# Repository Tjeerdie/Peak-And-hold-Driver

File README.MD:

# Project PWM peak and hold injector driver
The peak and hold project started because I could not find an open-source PWM peak and hold injector driver for low-Z injectors. For low-z injectors normally resistors in series with the injectors are used. But resistors create a lot of heat and are not very adjustable. 

I still do encourage everyone to use resistors if possible because the results are good and resistors have less components that can fail<br/>
<br/>
This design is specific to work with LPG injectors but could be used for any other low-Z injectors like TBI type and other high flow injectors. It could even be used for any coil type actuator like relays or valves <br/>

The board is designed in Kicad. So to see the schematic or to adjust the design to your liking open the Kicad project.<br/>

Latest release is V0.3.1<br/>
__IMPORANT NOTE: Board V0.3.1 is not tested yet!! A modified V0.3 is used for bench testing the V0.3.1 schematic. I did not test the board on a car yet__<br/>
__specifications:__
- Max peak current ~5A<br/>
- Max continuous hold current ~1A (No extra cooling)<br/>
- Max continuous hold current ~2A (With extra cooling)<br/>
- Hold PWM duty cycle 5%-95%<br/>
- PWM frequency 7khz<br/>
- 4 Individual injector channels<br/>
- Peak and hold current are adjustable

## Getting Started
This section explains all we need to do to setup a fabricated PCB

### Get all the parts
1. Order the PCB. For example use https://www.pcbway.com/ or https://jlcpcb.com/ Upload the PeakHoldPWMDriver_V0.x.y.zip located in the gebers folder and order the design.<br/>
2. Get all the parts from you favorite supplier. A BOM list is included in the geber folder<br/>
3. Assemble the PCB, hand soldering is possible.<br/>

### Connect the board
The board is intended to be connected to any ECU that uses a switch to ground for each injector channel. This is the case for most types of ECU. Further down this readme there is a description how to use microcontroller pins to drive the injectors directly. <br/>

__Connector J1__
1. injector channel 1 IN<br/>
2. injector channel 2 IN<br/>
3. injector channel 3 IN<br/>
4. injector channel 4 IN<br/>
5. Power - <br/>
6. Power + (14.8V switched with ignition switch)<br/>

__Connector J2__
1. inj channel 1 +<br/>
2. inj channel 1 -<br/>
3. inj channel 2 +<br/>
4. inj channel 2 -<br/>
5. inj channel 3 +<br/>
6. inj channel 3 -<br/>
7. inj channel 4 +<br/>
8. inj channel 4 -<br/>

Power on the board. Led must be lit when powered.<br/>

### Set the PEAK current
1. Measure __TP1__ and use __RV2__ to set to value needed. 100mV = 1A<br/>
2. Make sure this PEAK current is not too close to the maximum current. If that is the case you run the risk the peak current is never reached and the HOLD current is never set. Maximum advised peak current = 10.0[V] / R-inj[Ohm]<br/>

### Set the HOLD current
1. Measure the resistance of the injector(s) per channel (R-inj)[Ohm]. <br/>
2. Find the hold current needed for the injector in the datasheet. Usually about 50% to 25% of the peak current would be enough<br/>
3. Calculate the duty cycle needed using: ((R-inj + 0.20)* HoldCurrent)/2,4<br/>
4. Measure __TP2__ and use __RV1__ to set it to voltage calculated in step 3.<br/>
5. If it is possible in your setup or on a bench, connect __injector channel 1 IN__ to the __Power -__ use a multi-meter in series with your connected injector on channel 1 to measure the current. This must be close the the set current. If this is not correct adjust __RV1__ accordingly. Be careful when doing this test! When fuel pressure is present during testing the injector under test wil spray (a lot) of fuel! Its best to test with not pressurised injectors<br/>

### Direct microcontroller input
It is possible to use the board directly with an microcontroller. (non inverted inputs) The board inputs are designed for 5V. 3.3V can work but is on the edge so any voltage drop or temperature change may make it stop working correctly. <br/>

With a sharp object scratch the bridge between __pin 1__ and __pin 2__ of __JP1__, __JP2__, __JP3__, __JP4__ on the back of the board. Use a multi-meter to double check the connection is broken. Use a soldering iron and a bit of solder to connect __pin 3__ and __pin 2__ for __JP1__ to __JP4__. The second step is to remove R8, R25, R11, R28 from the board<br/> 
       
## Simulation	
An LTspice simulation of PWM peak and hold drivers is also in the LTspice folder. It is a good learning experience to see the wave forms and the current thru the coil. This also shows the maximum voltage level expected on the mosfets. This can be significant voltage levels depdending on the clamping voltage of the main driver. <br/>

## License
This project is licensed under the GNU GENERAL PUBLIC LICENSE - see the [LICENSE.md](LICENSE.md) file for details<br/>

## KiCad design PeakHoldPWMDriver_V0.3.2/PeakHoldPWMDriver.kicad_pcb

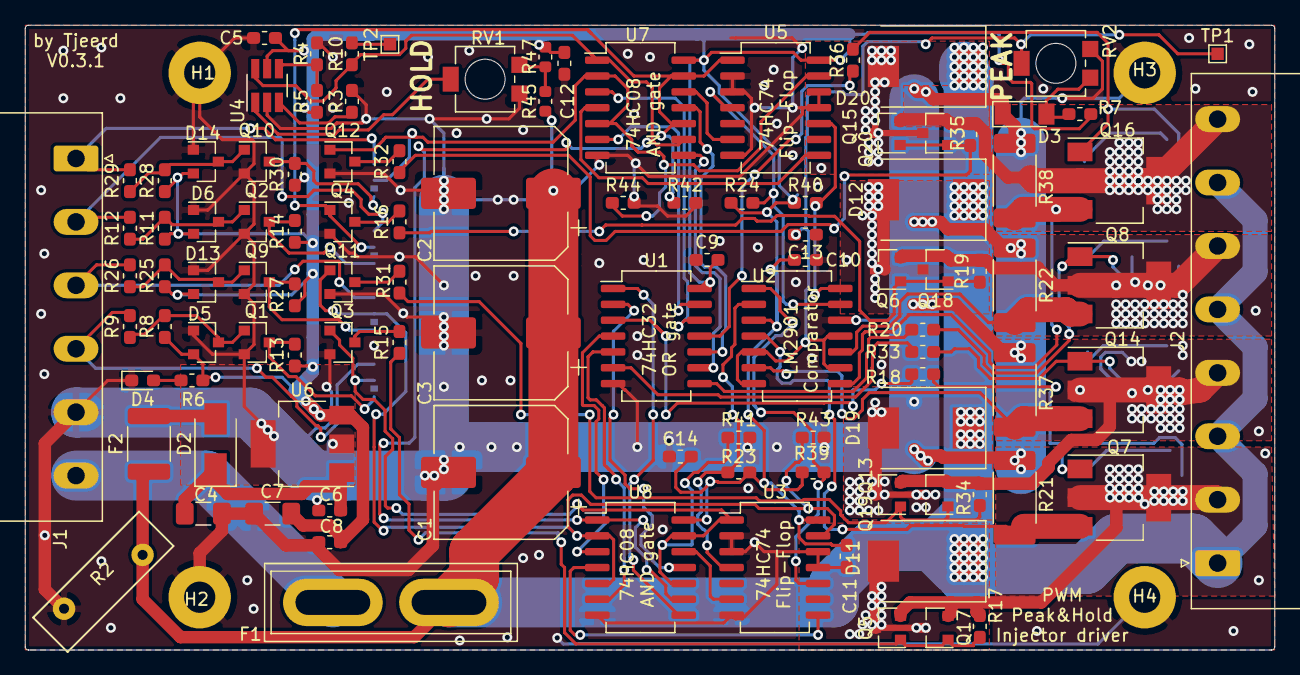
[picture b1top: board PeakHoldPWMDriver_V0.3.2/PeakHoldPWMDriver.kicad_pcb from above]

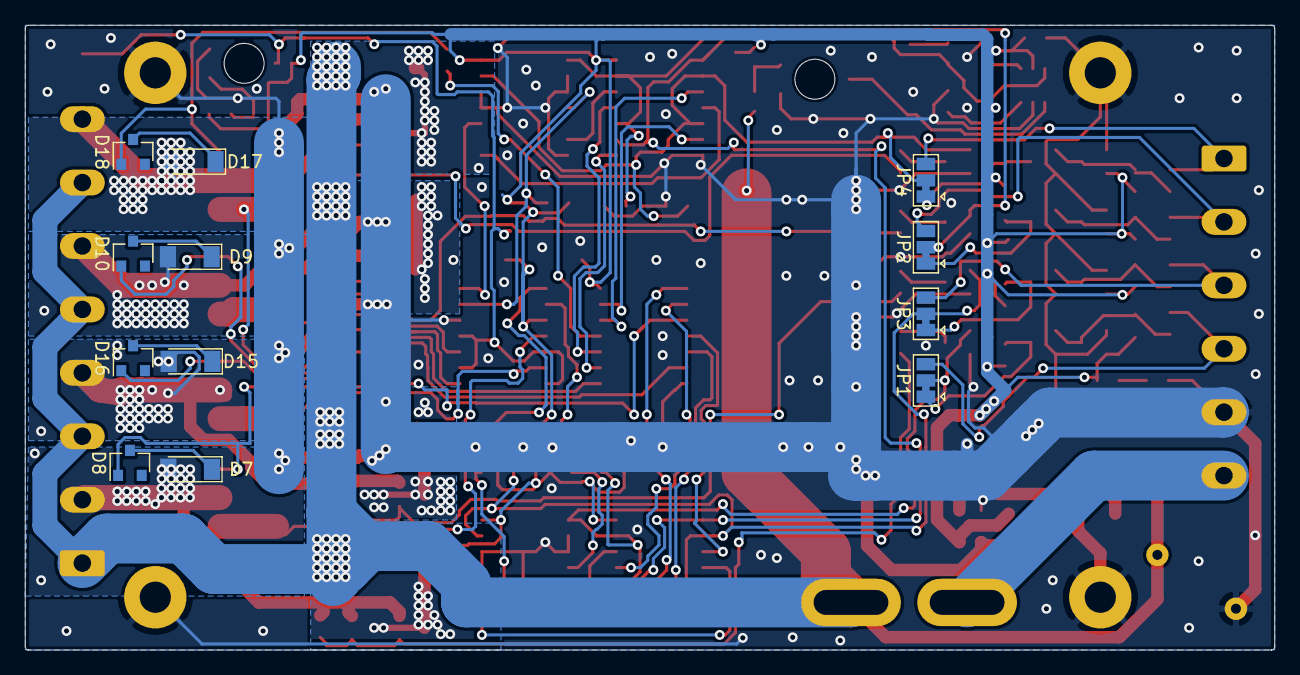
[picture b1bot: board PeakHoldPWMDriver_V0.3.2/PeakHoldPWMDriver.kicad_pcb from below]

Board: 2 copper layers, 100.1 x 50.0 mm, 122 parts (12 on the bottom side), 79 nets.

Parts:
C1, C2, C3: 1mF; CP_Elec_10x12.5
C4, C7: 10uf; C_1206_3216Metric_Pad1.42x1.75mm_HandSolder
C5, C6, C8, C9, C10, C11, C12, C13, C14: 220nf; C_0603_1608Metric_Pad1.05x0.95mm_HandSolder
D2: 1N4007; D_SMA
D3: LL4148; D_MiniMELF
D4: BLUE; LED_0603_1608Metric_Pad1.05x0.95mm_HandSolder
D5, D6, D13, D14: BAT54S; SOT-23
D7, D9, D15, D17: BAV103; D_MiniMELF
D8, D10, D16, D18: BZX84C39; D_SOT-23_ANK
D11, D12, D19, D20: SS36; D_SMC
F1: Fuse; Fuse_Blade_ATO_directSolder
F2: PPTC 16V2A; Fuse_1812_4532Metric_Pad1.30x3.40mm_HandSolder
H1, H2, H3, H4: MountingHole_Pad; MountingHole_2.5mm_Pad
J1: RND 205-00203; PhoenixContact_MSTBA_2,5_6-G-5,08_1x06_P5.08mm_Horizontal
J2: RND 205-00205; PhoenixContact_MSTBA_2,5_8-G-5,08_1x08_P5.08mm_Horizontal
JP1, JP2, JP3, JP4: SolderJumper_3_Bridged12; SolderJumper-3_P1.3mm_Bridged12_Pad1.0x1.5mm
Q1, Q2, Q3, Q4, Q9, Q10, Q11, Q12: 2N7002; SOT-23
Q5, Q6, Q13, Q15, Q17, Q18, Q19, Q20: TSM2309; SOT-23
Q7, Q8, Q14, Q16: IRLL 024N; SOT-223
R2: VARISTOR-18V; RV_Disc_D12mm_W3.9mm_P7.5mm
R3: 470k; R_0603_1608Metric_Pad1.05x0.95mm_HandSolder
R4: 100k; R_0603_1608Metric_Pad1.05x0.95mm_HandSolder
R5: 15k; R_0603_1608Metric_Pad1.05x0.95mm_HandSolder
R6, R7, R9, R12, R15, R16, R17, R19, R26, R29, R31, R32, R34, R35: 470R; R_0603_1608Metric_Pad1.05x0.95mm_HandSolder
R8, R11, R25, R28, R41, R43, R44: 10K; R_0603_1608Metric_Pad1.05x0.95mm_HandSolder
R10: 10k; R_0603_1608Metric_Pad1.05x0.95mm_HandSolder
R13, R14, R23, R24, R27, R30, R39, R40, R42: 1K; R_0603_1608Metric_Pad1.05x0.95mm_HandSolder
R18, R20, R33, R36: 100R; R_0603_1608Metric_Pad1.05x0.95mm_HandSolder
R21, R22, R37, R38: 0R1; R_2512_6332Metric_Pad1.52x3.35mm_HandSolder
R45: 120k; R_0603_1608Metric
R47: 33k; R_0603_1608Metric
RV1, RV2: 5K; Potentiometer_Bourns_3314R-1_Vertical_Hole
TP1: PeakTP; TestPoint_Pad_1.0x1.0mm
TP2: HoldTP; TestPoint_Pad_1.0x1.0mm
U1: 74HC32; SO-14_5.3x10.2mm_P1.27mm
U2: LM2901; SO-14_5.3x10.2mm_P1.27mm
U3, U5: 74HC74; SO-14_5.3x10.2mm_P1.27mm
U4: LTC6992; SOT-23-6_Handsoldering
U6: LM340; SOT-223-3_TabPin2
U7, U8: 74HC08; SO-14_5.3x10.2mm_P1.27mm

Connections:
5V: C5.1, C7.2, C8.2, C9.2, C10.2, C11.2, C12.2, C14.2, D5.2, D6.2, D13.2, D14.2, R5.1, R6.2, R7.1, R8.1, R11.1, R13.1, R14.1, R23.1, R24.1, R25.1, R27.1, R28.1, R30.1, R39.1, R40.1, R47.2, U1.14, U2.3, U3.14, U4.5, U5.14, U6.3, U7.14, U8.14
INJ1: J1.4, JP1.3, R9.2
INJ1-OUT: D7.2, J2.2, Q5.2, Q7.2, Q7.4, Q17.2, R17.2
INJ2: J1.3, JP3.3, R26.2
INJ2-OUT: D15.2, J2.4, Q13.2, Q14.2, Q14.4, Q19.2, R34.2
INJ3: J1.2, JP2.3, R12.2
INJ3-OUT: D9.2, J2.6, Q6.2, Q8.2, Q8.4, Q18.2, R19.2
INJ4: J1.1, JP4.3, R29.2
INJ4-OUT: D17.2, J2.8, Q15.2, Q16.2, Q16.4, Q20.2, R35.2
unnamed: C4.2, C6.2, D2.1, U6.1
unnamed: D2.2, F2.2
unnamed: D3.2, R7.2, RV2.1
unnamed: D4.2, R6.1
unnamed: D5.3, Q1.1, R8.2, R9.1
unnamed: D6.3, Q2.1, R11.2, R12.1
unnamed: D7.1, D8.1
unnamed: D8.2, Q7.1, R18.1
unnamed: D9.1, D10.1
unnamed: D10.2, Q8.1, R20.1
unnamed: D11.2, Q5.3, Q17.3
unnamed: D12.2, Q6.3, Q18.3
unnamed: D13.3, Q9.1, R25.2, R26.1
unnamed: D14.3, Q10.1, R28.2, R29.1
unnamed: D15.1, D16.1
unnamed: D16.2, Q14.1, R33.1
unnamed: D17.1, D18.1
unnamed: D18.2, Q16.1, R36.1
unnamed: D19.2, Q13.3, Q19.3
unnamed: D20.2, Q15.3, Q20.3
unnamed: JP1.1, Q1.3, R13.2
unnamed: JP2.1, Q2.3, R14.2
unnamed: JP3.1, Q9.3, R27.2
unnamed: JP4.1, Q10.3, R30.2
unnamed: Q3.3, R15.2
unnamed: Q4.3, R16.2
unnamed: Q7.3, R21.1, U2.4
unnamed: Q8.3, R22.1, U2.10
unnamed: Q11.3, R31.1
unnamed: Q12.3, R32.2
unnamed: Q13.1, Q19.1, R31.2, R34.1
unnamed: Q14.3, R37.1, U2.6
unnamed: Q15.1, Q20.1, R32.1, R35.1
unnamed: Q16.3, R38.1, U2.8
unnamed: Q5.1, Q17.1, R15.1, R17.1
unnamed: Q6.1, Q18.1, R16.1, R19.1
unnamed: R3.1, U4.3
unnamed: R4.2, R5.2, U4.4
unnamed: R10.1, TP2.1
unnamed: R18.2, U1.3
unnamed: R20.2, U1.8
unnamed: R23.2, U2.2, U3.4
unnamed: R24.2, U2.13, U5.4
unnamed: R33.2, U1.6
unnamed: R36.2, U1.11
unnamed: R39.2, U2.1, U3.10
unnamed: R40.2, U2.14, U5.10
unnamed: R45.2, R47.1, RV1.3
unnamed: RV1.2, U4.1
unnamed: U1.1, U8.8
unnamed: U1.2, U8.11
unnamed: U1.4, U8.3
unnamed: U1.5, U8.6
unnamed: U1.9, U7.8
unnamed: U1.10, U7.11
unnamed: U1.12, U7.3
unnamed: U1.13, U7.6
unnamed: U3.6, U8.12
unnamed: U3.8, U8.4
unnamed: U5.6, U7.12
unnamed: U5.8, U7.4
PWM: R10.2, U4.6, U7.1, U7.9, U8.1, U8.9
PWR_GND: C1.2, C2.2, C3.2, C4.1, C5.2, C6.1, C7.1, C8.1, C9.1, C10.1, C11.1, C12.1, C13.1, C14.1, D3.1, D4.1, D5.1, D6.1, D13.1, D14.1, H1.1, H2.1, H3.1, H4.1, J1.5, Q1.2, Q2.2, Q3.2, Q4.2, Q9.2, Q10.2, Q11.2, Q12.2, R2.1, R3.2, R4.1, R21.2, R22.2, R37.2, R38.2, R41.2, R42.2, R43.2, R44.2, RV1.1, RV2.3, U1.7, U2.12, U3.2, U3.3, U3.7, U3.11, U3.12, U4.2, U5.2, U5.3, U5.7, U5.11, U5.12, U6.2, U7.7, U8.7
VBAT: C1.1, C2.1, C3.1, D11.1, D12.1, D19.1, D20.1, F1.2, F2.1, J2.1, J2.3, J2.5, J2.7, R2.2, R45.1
VBAT_IN: F1.1, J1.6
VREF: C13.2, RV2.2, TP1.1, U2.5, U2.7, U2.9, U2.11
inv_INJ1: JP1.2, Q3.1, R41.1, U3.1, U8.10, U8.13
inv_INJ2: JP3.2, Q11.1, R43.1, U3.13, U8.2, U8.5
inv_INJ3: JP2.2, Q4.1, R42.1, U5.1, U7.10, U7.13
inv_INJ4: JP4.2, Q12.1, R44.1, U5.13, U7.2, U7.5

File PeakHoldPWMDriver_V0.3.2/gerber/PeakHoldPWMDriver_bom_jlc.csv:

"Comment","Designator","Footprint","LCSC Part #"
"1mF","C3,C2,C1","CP_Elec_10x12.5","C249474"
"220nf","C6,C5,C14,C12,C11,C10,C9,C13,C8","C_0603_1608Metric_Pad1.05x0.95mm_HandSolder","C21120"
"10uf","C7,C4","C_1206_3216Metric_Pad1.42x1.75mm_HandSolder","C13585"
"LL4148","D3","D_MiniMELF","C9808"
"BLUE","D4","LED_0603_1608Metric_Pad1.05x0.95mm_HandSolder","C375446"
"BAT54S","D6,D14,D13,D5","SOT-23","C19726"
"SS36","D20,D19,D12,D11","D_SMC","C35722"
"PPTC 16V2A","F2","Fuse_1812_4532Metric_Pad1.30x3.40mm_HandSolder","C70115"
"TSM2309","Q5,Q15,Q13,Q6,Q19,Q17,Q18,Q20","SOT-23","C15127"
"2N7002","Q12,Q11,Q4,Q1,Q2,Q10,Q9,Q3","SOT-23","C8545"
"IRLL 024N","Q16,Q14,Q8,Q7","SOT-223","C189606"
"470k","R3","R_0603_1608Metric_Pad1.05x0.95mm_HandSolder","C23178"
"100k","R4","R_0603_1608Metric_Pad1.05x0.95mm_HandSolder","C25803"
"15k","R5","R_0603_1608Metric_Pad1.05x0.95mm_HandSolder","C22809"
"470R","R6,R32,R35,R34,R16,R19,R15,R17,R7,R9,R12,R29,R31,R26","R_0603_1608Metric_Pad1.05x0.95mm_HandSolder","C23179"
"10K","R8,R11,R28,R25,R44,R43,R41","R_0603_1608Metric_Pad1.05x0.95mm_HandSolder","C25804"
"10k","R10","R_0603_1608Metric_Pad1.05x0.95mm_HandSolder","C25804"
"0R1","R22,R38,R21,R37","R_2512_6332Metric_Pad1.52x3.35mm_HandSolder","C76254"
"1K","R24,R39,R40,R23,R13,R14,R30,R27,R42","R_0603_1608Metric_Pad1.05x0.95mm_HandSolder","C21190"
"100R","R33,R36,R20,R18","R_0603_1608Metric_Pad1.05x0.95mm_HandSolder","C22775"
"120k","R45","R_0603_1608Metric","C25808"
"33k","R47","R_0603_1608Metric","C4216"
"74HC32","U1","SO-14_5.3x10.2mm_P1.27mm","C5632"
"LM2901","U2","SO-14_5.3x10.2mm_P1.27mm","C163545"
"LTC6992","U4","SOT-23-6_Handsoldering","C117381"
"74HC74","U5,U3","SO-14_5.3x10.2mm_P1.27mm","C7345"
"LM340","U6","SOT-223-3_TabPin2","C131990"
"74HC08","U7,U8","SO-14_5.3x10.2mm_P1.27mm","C5593"

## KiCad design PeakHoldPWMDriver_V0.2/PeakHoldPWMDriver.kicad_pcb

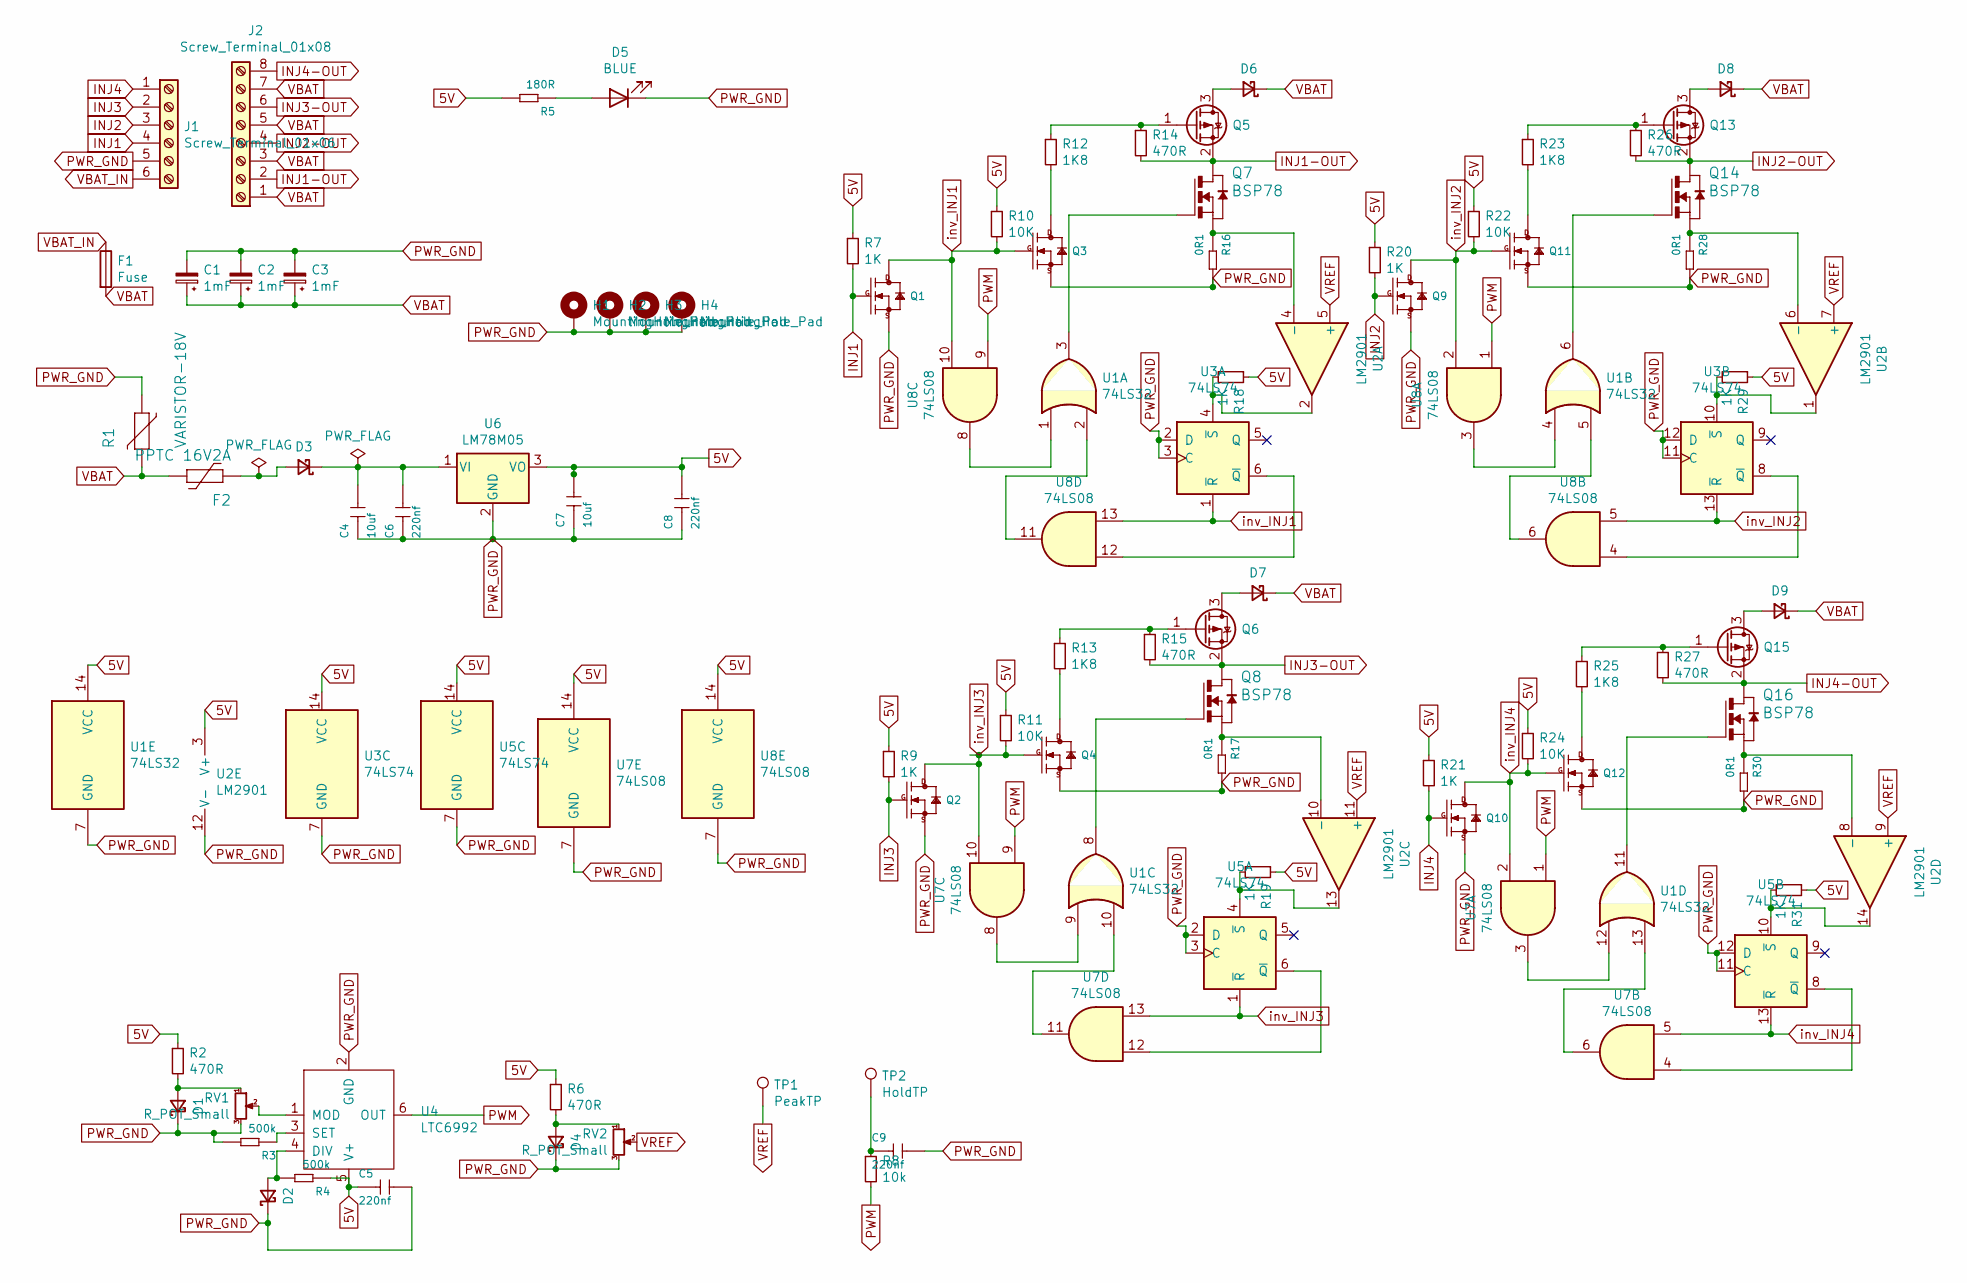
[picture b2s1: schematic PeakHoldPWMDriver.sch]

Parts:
C1, C2, C3: 1mF; CP_Elec_10x12.5
C4, C7: 10uf; C_1206_3216Metric_Pad1.42x1.75mm_HandSolder
C5, C6, C8, C9: 220nf; C_0603_1608Metric_Pad1.05x0.95mm_HandSolder
D1, D2, D4: BAV103; D_MiniMELF
D3: 1N4007; D_SMA
D5: BLUE; LED_0603_1608Metric_Pad1.05x0.95mm_HandSolder
D6, D7, D8, D9: SS36; D_SMA
F1: Fuse; Fuse_Blade_ATO_directSolder
F2: PPTC 16V2A; Fuse_1812_4532Metric_Pad1.30x3.40mm_HandSolder
H1, H2, H3, H4: MountingHole_Pad; MountingHole_2.5mm_Pad
J1: Screw_Terminal_01x06; PhoenixContact_MSTBA_2,5_6-G-5,08_1x06_P5.08mm_Horizontal
J2: Screw_Terminal_01x08; PhoenixContact_MSTBA_2,5_8-G-5,08_1x08_P5.08mm_Horizontal
Q1, Q2, Q9, Q10: AO3400; SOT-23_Handsoldering
Q3, Q4, Q11, Q12: 2N7002; SOT-23_Handsoldering
Q5, Q6, Q13, Q15: TSM2309; SOT-23_Handsoldering
Q7, Q8, Q14, Q16: BSP78; SOT-223
R1: VARISTOR-18V; RV_Disc_D12mm_W3.9mm_P7.5mm
R2, R6, R14, R15, R26, R27: 470R; R_0603_1608Metric_Pad1.05x0.95mm_HandSolder
R3, R4: 500k; R_0603_1608Metric_Pad1.05x0.95mm_HandSolder
R5: 180R; R_0603_1608Metric_Pad1.05x0.95mm_HandSolder
R7, R9, R18, R19, R20, R21, R29, R31: 1K; R_0603_1608Metric_Pad1.05x0.95mm_HandSolder
R8: 10k; R_0603_1608Metric_Pad1.05x0.95mm_HandSolder
R10, R11, R22, R24: 10K; R_0603_1608Metric_Pad1.05x0.95mm_HandSolder
R12, R13, R23, R25: 1K8; R_0603_1608Metric_Pad1.05x0.95mm_HandSolder
R16, R17, R28, R30: 0R1; R_2512_6332Metric_Pad1.52x3.35mm_HandSolder
RV1, RV2: R_POT_Small; Potentiometer_Bourns_3314R-1_Vertical_Hole
TP1: PeakTP; TestPoint_Pad_1.0x1.0mm
TP2: HoldTP; TestPoint_Pad_1.0x1.0mm
U1: 74LS32; SO-14_5.3x10.2mm_P1.27mm
U2: LM2901; SO-14_5.3x10.2mm_P1.27mm
U3, U5: 74LS74; SO-14_5.3x10.2mm_P1.27mm
U4: LTC6992; SOT-23-6_Handsoldering
U6: LM78M05; SOT-223-3_TabPin2
U7, U8: 74LS08; SO-14_5.3x10.2mm_P1.27mm

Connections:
5V: C5.1, C7.2, C8.2, R2.1, R4.1, R5.2, R6.1, R7.1, R9.1, R10.1, R11.1, R18.1, R19.1, R20.1, R21.1, R22.1, R24.1, R29.1, R31.1, U1.14 (VCC), U2.3 (V+), U3.14 (VCC), U4.5 (V+), U5.14 (VCC), U6.3 (VO), U7.14 (VCC), U8.14 (VCC)
INJ1: J1.4, Q1.1 (G), R7.2
INJ1-OUT: J2.2, Q5.2 (S), Q7.2 (D), Q7.4 (D), R14.2
INJ2: J1.3, Q9.1 (G), R20.2
INJ2-OUT: J2.4, Q13.2 (S), Q14.2 (D), Q14.4 (D), R26.2
INJ3: J1.2, Q2.1 (G), R9.2
INJ3-OUT: J2.6, Q6.2 (S), Q8.2 (D), Q8.4 (D), R15.2
INJ4: J1.1, Q10.1 (G), R21.2
INJ4-OUT: J2.8, Q15.2 (S), Q16.2 (D), Q16.4 (D), R27.2
unnamed: C4.2, C6.2, D3.1 (K), U6.1 (VI)
unnamed: C9.1, R8.1, TP2.1
unnamed: D1.2 (A), R2.2, RV1.1
unnamed: D2.2 (A), R4.2, U4.4 (DIV)
unnamed: D3.2 (A), F2.2
unnamed: D4.2 (A), R6.2, RV2.1
unnamed: D5.2 (A), R5.1
unnamed: D6.2 (A), Q5.3 (D)
unnamed: D7.2 (A), Q6.3 (D)
unnamed: D8.2 (A), Q13.3 (D)
unnamed: D9.2 (A), Q15.3 (D)
unnamed: Q3.3 (D), R12.2
unnamed: Q4.3 (D), R13.2
unnamed: Q5.1 (G), R12.1, R14.1
unnamed: Q6.1 (G), R13.1, R15.1
unnamed: Q7.1 (G), U1.3
unnamed: Q7.3 (S), R16.1, U2.4 (-)
unnamed: Q8.1 (G), U1.8
unnamed: Q8.3 (S), R17.1, U2.10 (-)
unnamed: Q11.3 (D), R23.2
unnamed: Q12.3 (D), R25.2
unnamed: Q13.1 (G), R23.1, R26.1
unnamed: Q14.1 (G), U1.6
unnamed: Q14.3 (S), R28.1, U2.6 (-)
unnamed: Q15.1 (G), R25.1, R27.1
unnamed: Q16.1 (G), U1.11
unnamed: Q16.3 (S), R30.1, U2.8 (-)
unnamed: R3.1, U4.3 (SET)
unnamed: R18.2, U2.2, U3.4 (~S)
unnamed: R19.2, U2.13, U5.4 (~S)
unnamed: R29.2, U2.1, U3.10 (~S)
unnamed: R31.2, U2.14, U5.10 (~S)
unnamed: RV1.2, U4.1 (MOD)
unnamed: U1.1, U8.8
unnamed: U1.2, U8.11
unnamed: U1.4, U8.3
unnamed: U1.5, U8.6
unnamed: U1.9, U7.8
unnamed: U1.10, U7.11
unnamed: U1.12, U7.3
unnamed: U1.13, U7.6
unnamed: U3.6 (~Q), U8.12
unnamed: U3.8 (~Q), U8.4
unnamed: U5.6 (~Q), U7.12
unnamed: U5.8 (~Q), U7.4
PWM: R8.2, U4.6 (OUT), U7.1, U7.9, U8.1, U8.9
PWR_GND: C1.2, C2.2, C3.2, C4.1, C5.2, C6.1, C7.1, C8.1, C9.2, D1.1 (K), D2.1 (K), D4.1 (K), D5.1 (K), H1.1, H2.1, H3.1, H4.1, J1.5, Q1.2 (S), Q2.2 (S), Q3.2 (S), Q4.2 (S), Q9.2 (S), Q10.2 (S), Q11.2 (S), Q12.2 (S), R1.1, R3.2, R16.2, R17.2, R28.2, R30.2, RV1.3, RV2.3, U1.7 (GND), U2.12 (V-), U3.2 (D), U3.3 (C), U3.7 (GND), U3.11 (C), U3.12 (D), U4.2 (GND), U5.2 (D), U5.3 (C), U5.7 (GND), U5.11 (C), U5.12 (D), U6.2 (GND), U7.7 (GND), U8.7 (GND)
VBAT: C1.1, C2.1, C3.1, D6.1 (K), D7.1 (K), D8.1 (K), D9.1 (K), F1.2, F2.1, J2.1, J2.3, J2.5, J2.7, R1.2
VBAT_IN: F1.1, J1.6
VREF: RV2.2, TP1.1, U2.5 (+), U2.7 (+), U2.9 (+), U2.11 (+)
inv_INJ1: Q1.3 (D), Q3.1 (G), R10.2, U3.1 (~R), U8.10, U8.13
inv_INJ2: Q9.3 (D), Q11.1 (G), R22.2, U3.13 (~R), U8.2, U8.5
inv_INJ3: Q2.3 (D), Q4.1 (G), R11.2, U5.1 (~R), U7.10, U7.13
inv_INJ4: Q10.3 (D), Q12.1 (G), R24.2, U5.13 (~R), U7.2, U7.5

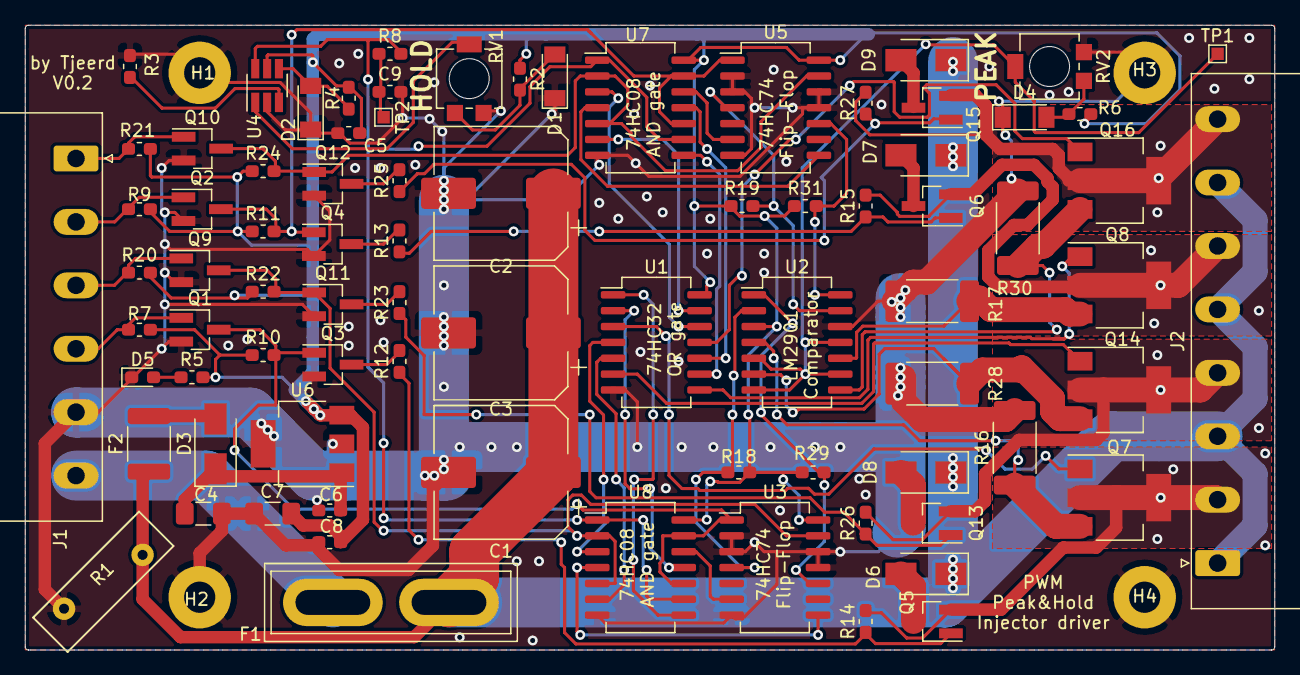
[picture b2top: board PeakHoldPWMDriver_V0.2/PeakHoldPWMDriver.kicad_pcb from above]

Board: 2 copper layers, 100.1 x 50.0 mm, 85 parts (0 on the bottom side), 63 nets.

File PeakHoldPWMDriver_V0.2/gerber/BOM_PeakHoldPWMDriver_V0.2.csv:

"Id";"Designator";"Package";"Quantity";"Designation";"Supplier and ref";
1;"D2,D4,D1";"D_MiniMELF";3;"BAV103";;;
2;"Q1,Q10,Q9,Q2";"SOT-23_Handsoldering";4;"AO3400";;;
3;"R22,R24,R11,R10";"R_0603_1608Metric_Pad1.05x0.95mm_HandSolder";4;"10K";;;
4;"U8,U7";"SO-14_5.3x10.2mm_P1.27mm";2;"74LS08";;;
5;"U3,U5";"SO-14_5.3x10.2mm_P1.27mm";2;"74LS74";;;
6;"R16,R17,R30,R28";"R_2512_6332Metric_Pad1.52x3.35mm_HandSolder";4;"0R1";;;
7;"Q15,Q6,Q5,Q13";"SOT-23_Handsoldering";4;"TSM2309";;;
8;"J1";"PhoenixContact_MSTBA_2,5_6-G-5,08_1x06_P5.08mm_Horizontal";1;"Screw_Terminal_01x06";;;
9;"J2";"PhoenixContact_MSTBA_2,5_8-G-5,08_1x08_P5.08mm_Horizontal";1;"Screw_Terminal_01x08";;;
10;"H4,H3,H2,H1";"MountingHole_2.5mm_Pad";4;"MountingHole_Pad";;;
11;"D3";"D_SMA";1;"1N4007";;;
12;"D9,D8,D7,D6";"D_SMA";4;"SS36";;;
13;"U6";"SOT-223-3_TabPin2";1;"LM78M05";;;
14;"TP2";"TestPoint_Pad_1.0x1.0mm";1;"HoldTP";;;
15;"TP1";"TestPoint_Pad_1.0x1.0mm";1;"PeakTP";;;
16;"R8";"R_0603_1608Metric_Pad1.05x0.95mm_HandSolder";1;"10k";;;
17;"C10,C6,C9,C7";"C_0603_1608Metric_Pad1.05x0.95mm_HandSolder";4;"220nf";;;
18;"C3,C2,C1";"CP_Elec_10x12.5";3;"1mF";;;
19;"U1";"SO-14_5.3x10.2mm_P1.27mm";1;"74LS32";;;
20;"D5";"LED_0603_1608Metric_Pad1.05x0.95mm_HandSolder";1;"BLUE";;;
21;"Q16,Q14,Q8,Q7";"SOT-223";4;"BSP78";;;
22;"R15,R14,R2,R6,R27,R26";"R_0603_1608Metric_Pad1.05x0.95mm_HandSolder";6;"470R";;;
23;"R13,R12,R25,R23";"R_0603_1608Metric_Pad1.05x0.95mm_HandSolder";4;"1K8";;;
24;"R21,R20,R9,R7,R31,R29,R19,R18";"R_0603_1608Metric_Pad1.05x0.95mm_HandSolder";8;"1K";;;
25;"Q3,Q12,Q11,Q4";"SOT-23_Handsoldering";4;"2N7002";;;
26;"F1";"Fuse_Blade_ATO_directSolder";1;"Fuse";;;
27;"F2";"Fuse_1812_4532Metric_Pad1.30x3.40mm_HandSolder";1;"PPTC 16V2A";;;
28;"C8,C5";"C_1206_3216Metric_Pad1.42x1.75mm_HandSolder";2;"10uf";;;
29;"U4";"SOT-23-6_Handsoldering";1;"LTC6992";;;
30;"U2";"SO-14_5.3x10.2mm_P1.27mm";1;"LM2901";;;
31;"RV1,RV2";"Potentiometer_Bourns_3314R-1_Vertical_Hole";2;"R_POT_Small";;;
32;"R4,R3";"R_0603_1608Metric_Pad1.05x0.95mm_HandSolder";2;"500k";;;
33;"R5";"R_0603_1608Metric_Pad1.05x0.95mm_HandSolder";1;"180R";;;
34;"R1";"RV_Disc_D12mm_W3.9mm_P7.5mm";1;"VARISTOR-18V";;;

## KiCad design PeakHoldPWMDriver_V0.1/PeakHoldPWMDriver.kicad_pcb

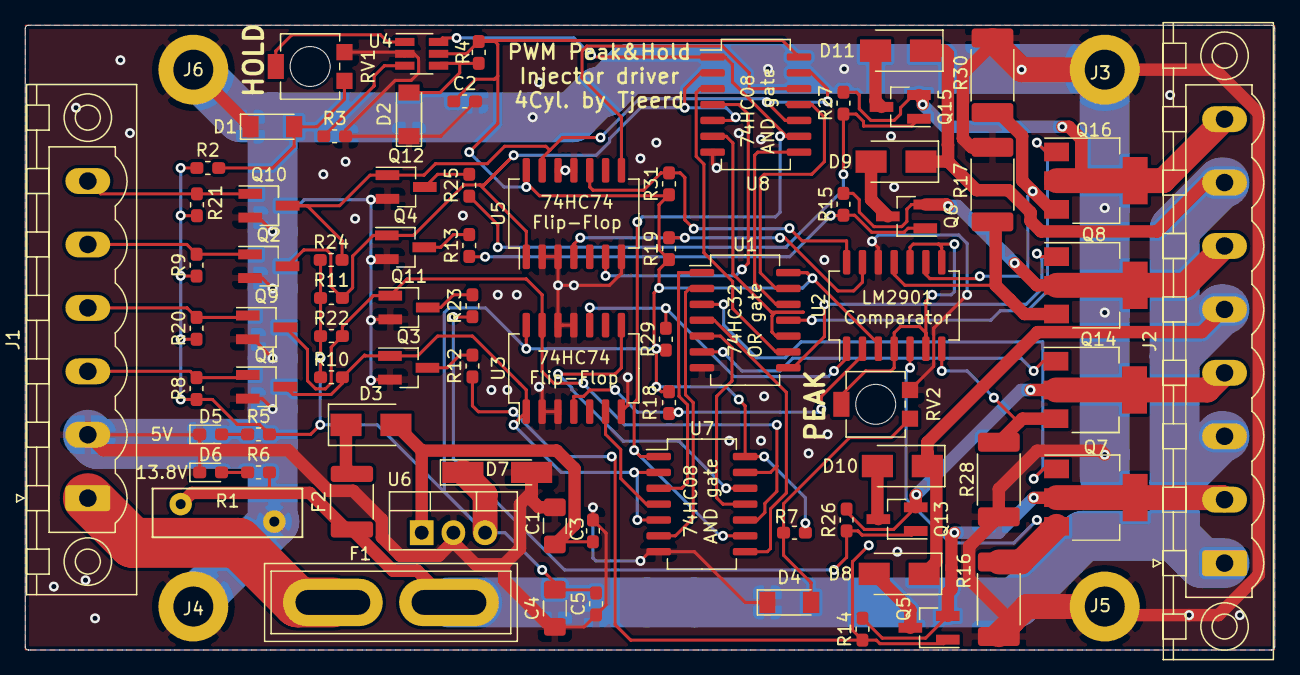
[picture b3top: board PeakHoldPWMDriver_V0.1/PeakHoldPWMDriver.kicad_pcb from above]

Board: 2 copper layers, 100.1 x 50.0 mm, 81 parts (0 on the bottom side), 63 nets.

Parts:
C1, C4: 10uf; C_1206_3216Metric_Pad1.42x1.75mm_HandSolder
C2, C3, C5: 220nf; C_0603_1608Metric_Pad1.05x0.95mm_HandSolder
D1, D4: LL4148; D_MiniMELF
D2: SS310; D_MiniMELF
D3: 40V-1A; D_SMA
D5, D6: BLUE; LED_0603_1608Metric_Pad1.05x0.95mm_HandSolder
D7: D_Zener_Small; D_MiniMELF_Handsoldering
D8, D9, D10, D11: SS310; D_SMA
F1: Fuse; Fuse_Blade_ATO_directSolder
F2: PPTC 16V2A; Fuse_1812_4532Metric_Pad1.30x3.40mm_HandSolder
J1: Screw_Terminal_01x06; PhoenixContact_MSTBV_2,5_6-GF-5,08_1x06_P5.08mm_Vertical_Th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
J2: Screw_Terminal_01x08; PhoenixContact_MSTBV_2,5_8-GF-5,08_1x08_P5.08mm_Vertical_Th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
J3, J4, J5, J6: Mounting 3mm; MountingHole_3.2mm_M3_DIN965_Pad
Q1, Q2, Q9, Q10: AO3400; SOT-23_Handsoldering
Q3, Q4, Q11, Q12: AO3422; SOT-23_Handsoldering
Q5, Q6, Q13, Q15: AO3401A; SOT-23_Handsoldering
Q7, Q8, Q14, Q16: BSP78; SOT-223
R1: VARISTOR-18V; RV_Disc_D12mm_W3.9mm_P7.5mm
R2, R7, R14, R15, R26, R27: 470; R_0603_1608Metric_Pad1.05x0.95mm_HandSolder
R3, R4: 500k; R_0603_1608Metric_Pad1.05x0.95mm_HandSolder
R5: 180; R_0603_1608Metric_Pad1.05x0.95mm_HandSolder
R6: 560; R_0603_1608Metric_Pad1.05x0.95mm_HandSolder
R8, R9, R18, R19, R20, R21, R29, R31: 1K; R_0603_1608Metric_Pad1.05x0.95mm_HandSolder
R10, R11, R22, R24: 10K; R_0603_1608Metric_Pad1.05x0.95mm_HandSolder
R12, R13, R23, R25: 1K8; R_0603_1608Metric_Pad1.05x0.95mm_HandSolder
R16, R17, R28, R30: 0R1; R_2512_6332Metric_Pad1.52x3.35mm_HandSolder
RV1, RV2: R_POT_Small; Potentiometer_Bourns_3314R-1_Vertical_Hole
U1: 74LS32; SO-14_5.3x10.2mm_P1.27mm
U2: LM2901; SO-14_5.3x10.2mm_P1.27mm
U3, U5: 74LS74; SO-14_5.3x10.2mm_P1.27mm
U4: LTC6992; SOT-23-6_Handsoldering
U6: LM78M05_TO220; TO-220-3_Vertical
U7, U8: 74LS08; SO-14_5.3x10.2mm_P1.27mm

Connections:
5V: C2.1, C4.2, C5.2, D7.1, R2.1, R4.1, R5.2, R7.1, R8.1, R9.1, R10.1, R11.1, R18.1, R19.1, R20.1, R21.1, R22.1, R24.1, R29.1, R31.1, U1.14, U2.3, U3.14, U4.5, U5.14, U6.3, U7.14, U8.14
INJ1: J1.3, Q1.1, R8.2
INJ1-OUT: J2.2, Q5.2, Q7.2, Q7.4, R14.2
INJ2: J1.4, Q9.1, R20.2
INJ2-OUT: J2.4, Q13.2, Q14.2, Q14.4, R26.2
INJ3: J1.5, Q2.1, R9.2
INJ3-OUT: J2.6, Q6.2, Q8.2, Q8.4, R15.2
INJ4: J1.6, Q10.1, R21.2
INJ4-OUT: J2.8, Q15.2, Q16.2, Q16.4, R27.2
unnamed: C1.2, C3.2, D3.2, U6.1
unnamed: D1.2, R2.2, RV1.1
unnamed: D2.2, R4.2, U4.4
unnamed: D3.1, F2.2
unnamed: D4.2, R7.2, RV2.1
unnamed: D5.2, R5.1
unnamed: D6.2, R6.1
unnamed: D8.2, Q5.3
unnamed: D9.2, Q6.3
unnamed: D10.2, Q13.3
unnamed: D11.2, Q15.3
unnamed: Q3.3, R12.2
unnamed: Q4.3, R13.2
unnamed: Q5.1, R12.1, R14.1
unnamed: Q6.1, R13.1, R15.1
unnamed: Q7.1, U1.3
unnamed: Q7.3, R16.1, U2.5
unnamed: Q8.1, U1.8
unnamed: Q8.3, R17.1, U2.11
unnamed: Q11.3, R23.2
unnamed: Q12.3, R25.2
unnamed: Q13.1, R23.1, R26.1
unnamed: Q14.1, U1.6
unnamed: Q14.3, R28.1, U2.7
unnamed: Q15.1, R25.1, R27.1
unnamed: Q16.1, U1.11
unnamed: Q16.3, R30.1, U2.9
unnamed: R3.1, U4.3
unnamed: R18.2, U2.2, U3.4
unnamed: R19.2, U2.13, U5.4
unnamed: R29.2, U2.1, U3.10
unnamed: R31.2, U2.14, U5.10
unnamed: RV1.2, U4.1
unnamed: U1.1, U7.3
unnamed: U1.2, U7.6
unnamed: U1.4, U7.8
unnamed: U1.5, U7.11
unnamed: U1.9, U8.3
unnamed: U1.10, U8.6
unnamed: U1.12, U8.8
unnamed: U1.13, U8.11
unnamed: U3.6, U7.4
unnamed: U3.8, U7.12
unnamed: U5.6, U8.4
unnamed: U5.8, U8.12
PWM: U4.6, U7.1, U7.9, U8.1, U8.9
PWR_GND: C1.1, C2.2, C3.1, C4.1, C5.1, D1.1, D2.1, D4.1, D5.1, D6.1, D7.2, J1.2, J3.1, J4.1, J5.1, J6.1, Q1.2, Q2.2, Q3.2, Q4.2, Q9.2, Q10.2, Q11.2, Q12.2, R1.1, R3.2, R16.2, R17.2, R28.2, R30.2, RV1.3, RV2.3, U1.7, U2.12, U3.2, U3.3, U3.7, U3.11, U3.12, U4.2, U5.2, U5.3, U5.7, U5.11, U5.12, U6.2, U7.7, U8.7
VBAT: D8.1, D9.1, D10.1, D11.1, F1.2, F2.1, J2.1, J2.3, J2.5, J2.7, R1.2, R6.2
VBAT_IN: F1.1, J1.1
VREF: RV2.2, U2.4, U2.6, U2.8, U2.10
inv_INJ1: Q1.3, Q3.1, R10.2, U3.1, U7.2, U7.5
inv_INJ2: Q9.3, Q11.1, R22.2, U3.13, U7.10, U7.13
inv_INJ3: Q2.3, Q4.1, R11.2, U5.1, U8.2, U8.5
inv_INJ4: Q10.3, Q12.1, R24.2, U5.13, U8.10, U8.13

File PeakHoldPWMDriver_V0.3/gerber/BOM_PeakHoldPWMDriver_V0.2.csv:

"Id";"Designator";"Package";"Quantity";"Designation";"Supplier and ref";
1;"D2,D4,D1";"D_MiniMELF";3;"BAV103";;;
2;"Q1,Q10,Q9,Q2";"SOT-23_Handsoldering";4;"AO3400";;;
3;"R22,R24,R11,R10";"R_0603_1608Metric_Pad1.05x0.95mm_HandSolder";4;"10K";;;
4;"U8,U7";"SO-14_5.3x10.2mm_P1.27mm";2;"74LS08";;;
5;"U3,U5";"SO-14_5.3x10.2mm_P1.27mm";2;"74LS74";;;
6;"R16,R17,R30,R28";"R_2512_6332Metric_Pad1.52x3.35mm_HandSolder";4;"0R1";;;
7;"Q15,Q6,Q5,Q13";"SOT-23_Handsoldering";4;"TSM2309";;;
8;"J1";"PhoenixContact_MSTBA_2,5_6-G-5,08_1x06_P5.08mm_Horizontal";1;"Screw_Terminal_01x06";;;
9;"J2";"PhoenixContact_MSTBA_2,5_8-G-5,08_1x08_P5.08mm_Horizontal";1;"Screw_Terminal_01x08";;;
10;"H4,H3,H2,H1";"MountingHole_2.5mm_Pad";4;"MountingHole_Pad";;;
11;"D3";"D_SMA";1;"1N4007";;;
12;"D9,D8,D7,D6";"D_SMA";4;"SS36";;;
13;"U6";"SOT-223-3_TabPin2";1;"LM78M05";;;
14;"TP2";"TestPoint_Pad_1.0x1.0mm";1;"HoldTP";;;
15;"TP1";"TestPoint_Pad_1.0x1.0mm";1;"PeakTP";;;
16;"R8";"R_0603_1608Metric_Pad1.05x0.95mm_HandSolder";1;"10k";;;
17;"C9,C5,C8,C6";"C_0603_1608Metric_Pad1.05x0.95mm_HandSolder";4;"220nf";;;
18;"C3,C2,C1";"CP_Elec_10x12.5";3;"1mF";;;
19;"U1";"SO-14_5.3x10.2mm_P1.27mm";1;"74LS32";;;
20;"D5";"LED_0603_1608Metric_Pad1.05x0.95mm_HandSolder";1;"BLUE";;;
21;"Q16,Q14,Q8,Q7";"SOT-223";4;"BSP78";;;
22;"R15,R14,R2,R6,R27,R26";"R_0603_1608Metric_Pad1.05x0.95mm_HandSolder";6;"470R";;;
23;"R13,R12,R25,R23";"R_0603_1608Metric_Pad1.05x0.95mm_HandSolder";4;"1K8";;;
24;"R21,R20,R9,R7,R31,R29,R19,R18";"R_0603_1608Metric_Pad1.05x0.95mm_HandSolder";8;"1K";;;
25;"Q3,Q12,Q11,Q4";"SOT-23_Handsoldering";4;"2N7002";;;
26;"F1";"Fuse_Blade_ATO_directSolder";1;"Fuse";;;
27;"F2";"Fuse_1812_4532Metric_Pad1.30x3.40mm_HandSolder";1;"PPTC 16V2A";;;
28;"C7,C4";"C_1206_3216Metric_Pad1.42x1.75mm_HandSolder";2;"10uf";;;
29;"U4";"SOT-23-6_Handsoldering";1;"LTC6992";;;
30;"U2";"SO-14_5.3x10.2mm_P1.27mm";1;"LM2901";;;
31;"RV1,RV2";"Potentiometer_Bourns_3314R-1_Vertical_Hole";2;"R_POT_Small";;;
32;"R4,R3";"R_0603_1608Metric_Pad1.05x0.95mm_HandSolder";2;"500k";;;
33;"R5";"R_0603_1608Metric_Pad1.05x0.95mm_HandSolder";1;"180R";;;
34;"R1";"RV_Disc_D12mm_W3.9mm_P7.5mm";1;"VARISTOR-18V";;;

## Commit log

2020-07-13 Initial commit
    First commit after making a separate repository for the peak and hold driver.
2020-07-13 Routing board V0.2
    Work done on new PCB
2020-07-14 routed V0.2
    New board fully routed
2020-07-14 updated readnme
2020-07-16 Cleanup of board
2020-07-19 further clean-up
2020-07-19 renumber all parts
2020-07-29 Started on V0.3
    - update on simulation
    - started design V0.3
    - input protection
    - Zener clamping on mosfet gate
2020-07-29 cleaup
    cleanup of silkscreen
2020-07-31 Added jumpers to choose between ECU or transistor input
2020-07-31 clean-up pcb
2020-08-01 Updates on V0.3
    Updated V0.3
    - Created readme
    - Cleaned up baord.
    - Created gerbers
2020-08-02 Added supplier to BOM list
2020-08-04 Update V0.3 PCB
    Updated V0.3 pcb with pulldown resistors when using ECU input. And some Cleanup pcb
2020-08-04 Update zener value
2020-08-05 update on p-chan mosfets
    Overheating issues hopefully solved by this mod
2020-08-07 Updates on schematic and pcb because of heat
2020-08-07 Simulating 2 pmos fets as high side driver
2020-08-07 Added battery voltage compensation to the simulation
2020-08-07 PCB and schematic updated with battery voltage compensation
2020-08-07 Some leftover updates
2020-08-09 updates on the simulation side again
2020-09-01 updates values on 0.3 added 0.3.1
    Updated resistor values for V0.3
    Added V0.3.1 with new battery voltage compensation
2020-09-01 Add scope images
2020-09-05 Update pictures
2020-09-06 Add pdf schematic
2020-09-13 Changed resistor value R5, now correct PWM freqency
2020-10-07 Add version V0.3.2
2020-11-11 Update schematic for clarity
2021-02-08 Update schematic with JLCPCB part numbers Added position csv and BOM files in JLCPCB placement list format
2021-02-08 Added position csv and BOM files in JLCPCB placement list format
2021-03-12 fix absolute path liberary troubles.
